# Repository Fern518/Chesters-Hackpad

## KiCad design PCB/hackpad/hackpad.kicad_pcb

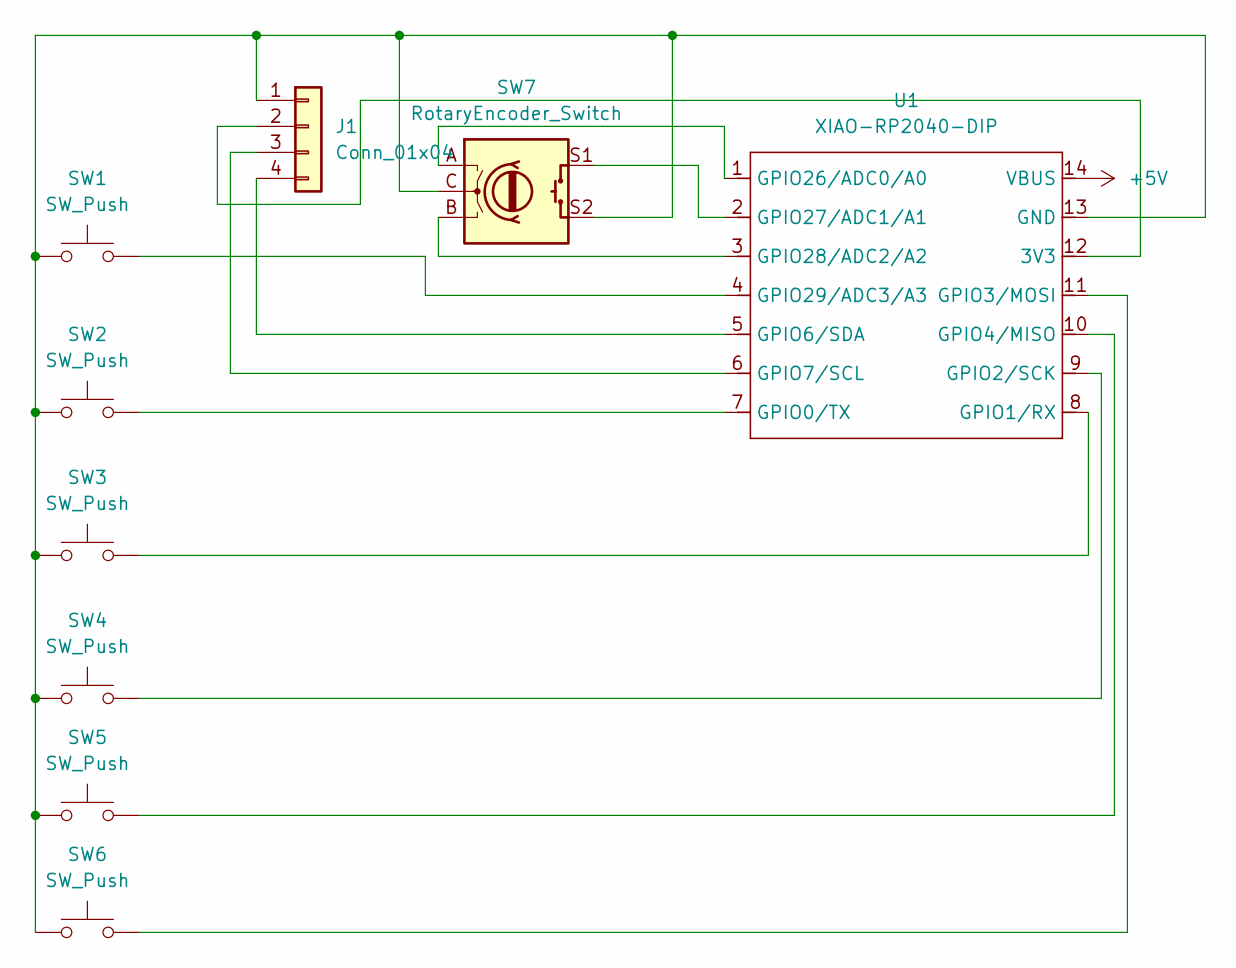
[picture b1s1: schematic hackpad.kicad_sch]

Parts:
J1: Conn_01x04; PinHeader_1x04_P2.54mm_Vertical
SW1, SW2, SW3, SW4, SW5, SW6: SW_Push; SW_Cherry_MX_1.00u_PCB
SW7: RotaryEncoder_Switch; RotaryEncoder_Alps_EC11E-Switch_Vertical_H20mm
U1: XIAO-RP2040-DIP

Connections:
+5V: U1.14 (VBUS)
unnamed: J1.1, SW1.1, SW2.1, SW3.1, SW4.1, SW5.1, SW6.1, SW7.C, SW7.S2, U1.13 (GND)
unnamed: J1.2, U1.12 (3V3)
unnamed: J1.3, U1.6 (GPIO7/SCL)
unnamed: J1.4, U1.5 (GPIO6/SDA)
unnamed: SW2.2, U1.7 (GPIO0/TX)
unnamed: SW3.2, U1.8 (GPIO1/RX)
unnamed: SW4.2, U1.9 (GPIO2/SCK)
unnamed: SW6.2, U1.11 (GPIO3/MOSI)
unnamed: SW5.2, U1.10 (GPIO4/MISO)
unnamed: SW7.A, U1.1 (GPIO26/ADC0/A0)
unnamed: SW7.S1, U1.2 (GPIO27/ADC1/A1)
unnamed: SW7.B, U1.3 (GPIO28/ADC2/A2)
unnamed: SW1.2, U1.4 (GPIO29/ADC3/A3)

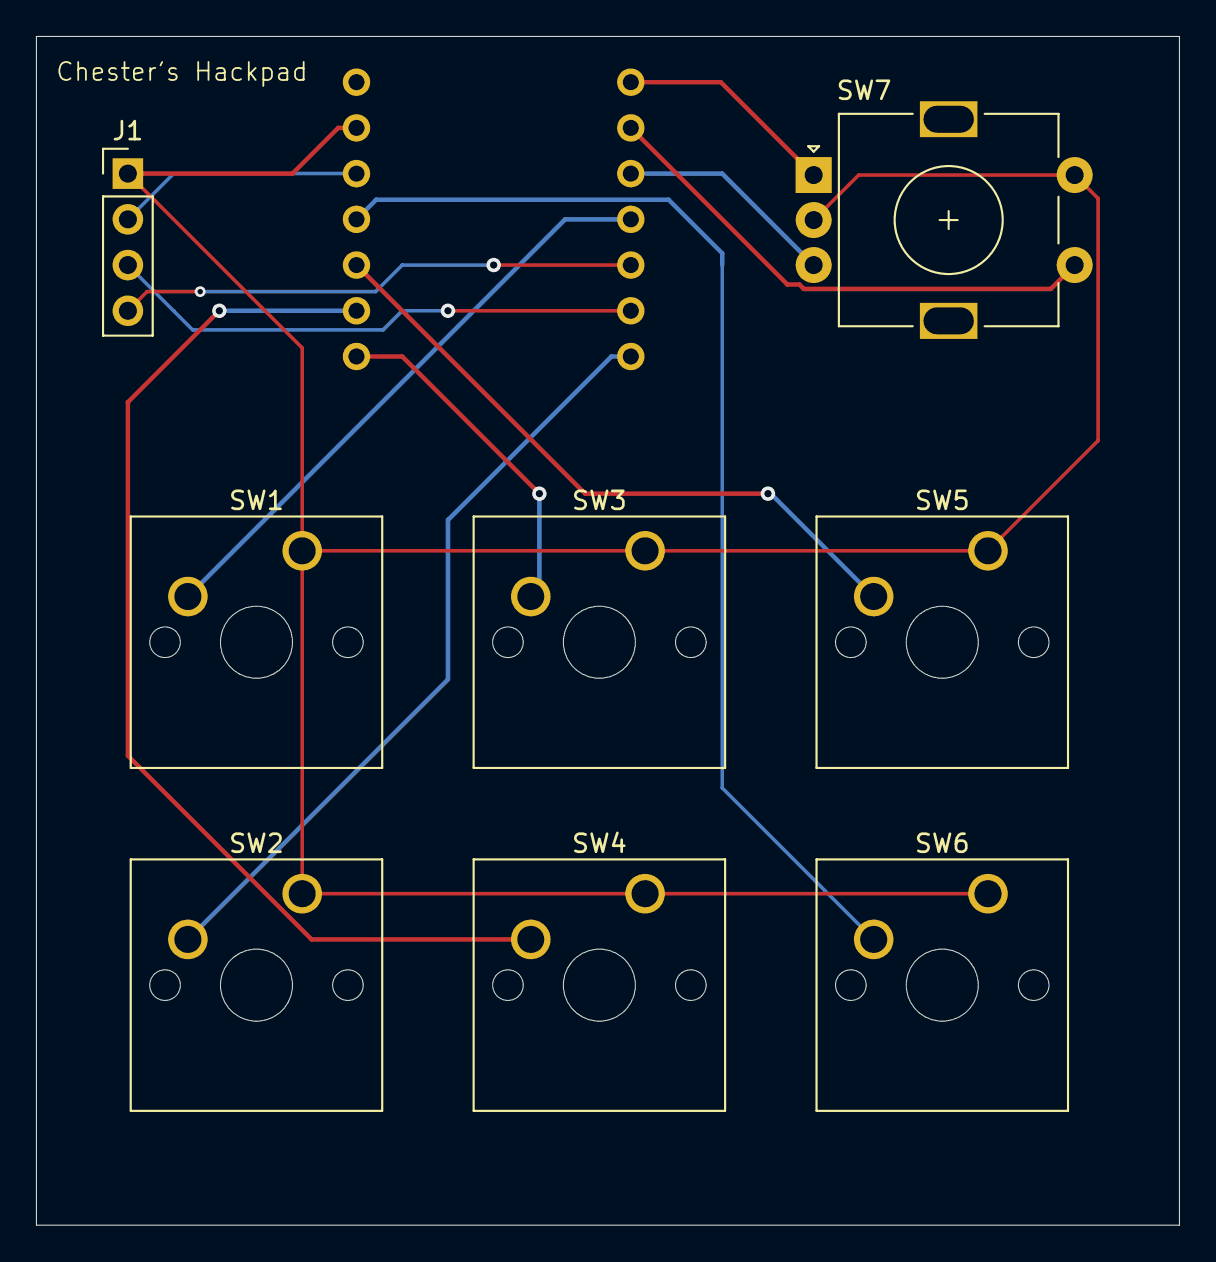
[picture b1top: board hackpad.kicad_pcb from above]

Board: 2 copper layers, 63.5 x 66.0 mm, 9 parts (1 on the bottom side), 13 nets.

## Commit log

2025-12-06 Added OPL Library and designed PCB
2025-12-06 Moved XIAO Microcontroller to back
    This change was made to avoid any physical overlap with the 1inch OLED display
2025-12-06 Added branding to board
    +Cleaned up a few connections
2025-12-06 Started work on case
2025-12-06 Designed top of case
    +added engravings to bottom of case
2025-12-07 Added basic firmware
2025-12-09 Added STEP files per request
2025-12-10 Added gerber filed for PCB
